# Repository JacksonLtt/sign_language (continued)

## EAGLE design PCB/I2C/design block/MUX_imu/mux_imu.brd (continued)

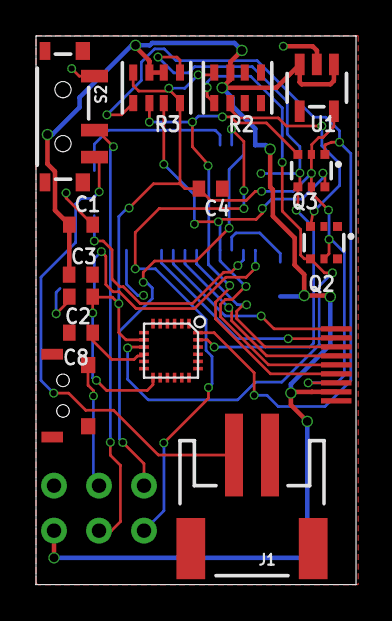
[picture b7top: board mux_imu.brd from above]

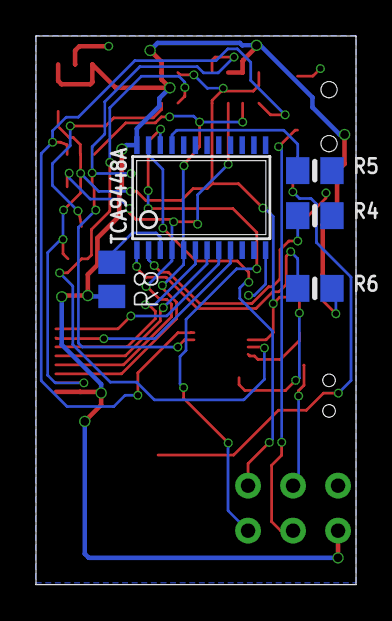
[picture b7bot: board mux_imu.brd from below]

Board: 2 copper layers, 17.8 x 30.5 mm, 26 parts (5 on the bottom side), 23 nets.

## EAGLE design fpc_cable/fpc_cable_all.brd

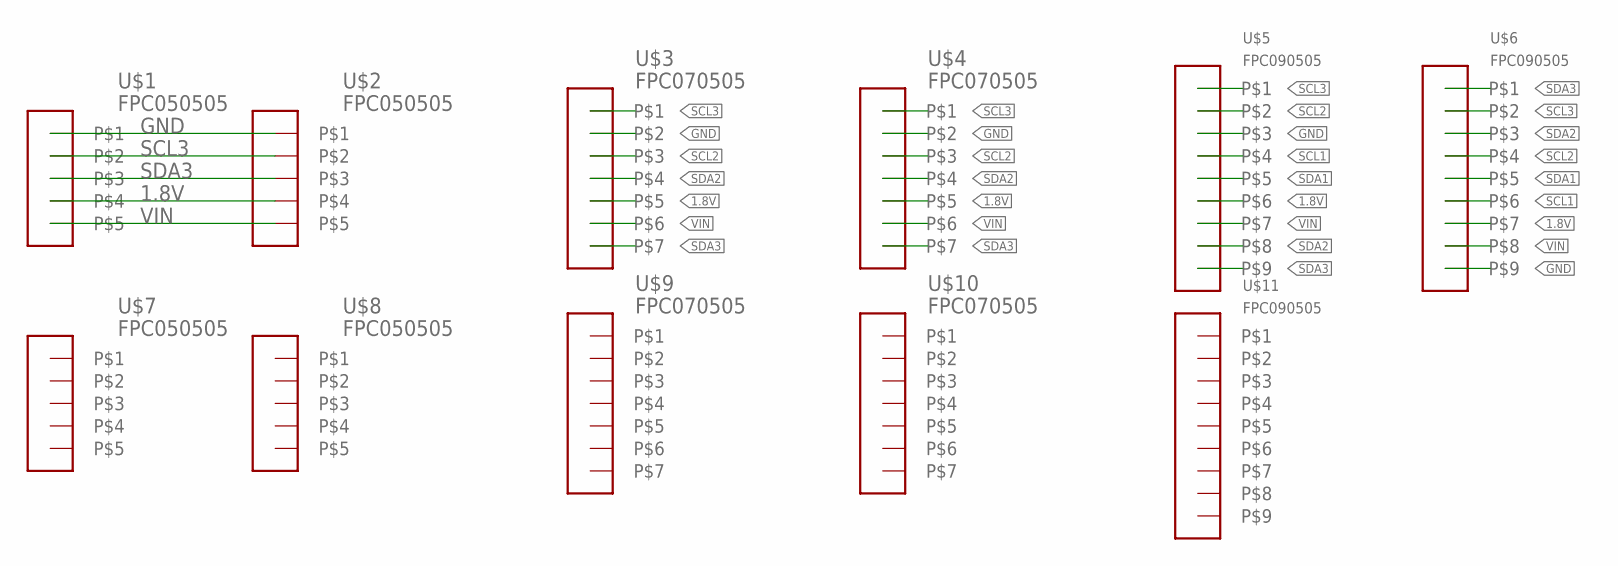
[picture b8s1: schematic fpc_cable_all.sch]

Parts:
U$1, U$2, U$7, U$8: FPC050505; FPC0505
U$3, U$4, U$9, U$10: FPC070505; FPC0705
U$5, U$6, U$11: FPC090505; FPC0905

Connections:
1.8V: U$1.P$4, U$2.P$4, U$3.P$5, U$4.P$5, U$5.P$6, U$6.P$7
GND: U$1.P$1, U$2.P$1, U$3.P$2, U$4.P$2, U$5.P$3, U$6.P$9
SCL1: U$5.P$4, U$6.P$6
SCL2: U$3.P$3, U$4.P$3, U$5.P$2, U$6.P$4
SCL3: U$1.P$2, U$2.P$2, U$3.P$1, U$4.P$1, U$5.P$1, U$6.P$2
SDA1: U$5.P$5, U$6.P$5
SDA2: U$3.P$4, U$4.P$4, U$5.P$8, U$6.P$3
SDA3: U$1.P$3, U$2.P$3, U$3.P$7, U$4.P$7, U$5.P$9, U$6.P$1
VIN: U$1.P$5, U$2.P$5, U$3.P$6, U$4.P$6, U$5.P$7, U$6.P$8

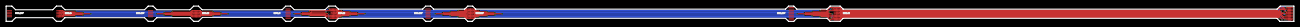
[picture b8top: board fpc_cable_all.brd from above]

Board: 2 copper layers, 422.3 x 5.0 mm, 11 parts (0 on the bottom side), 9 nets.

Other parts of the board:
IMU6_OUT: FPC050505; FPC0505
